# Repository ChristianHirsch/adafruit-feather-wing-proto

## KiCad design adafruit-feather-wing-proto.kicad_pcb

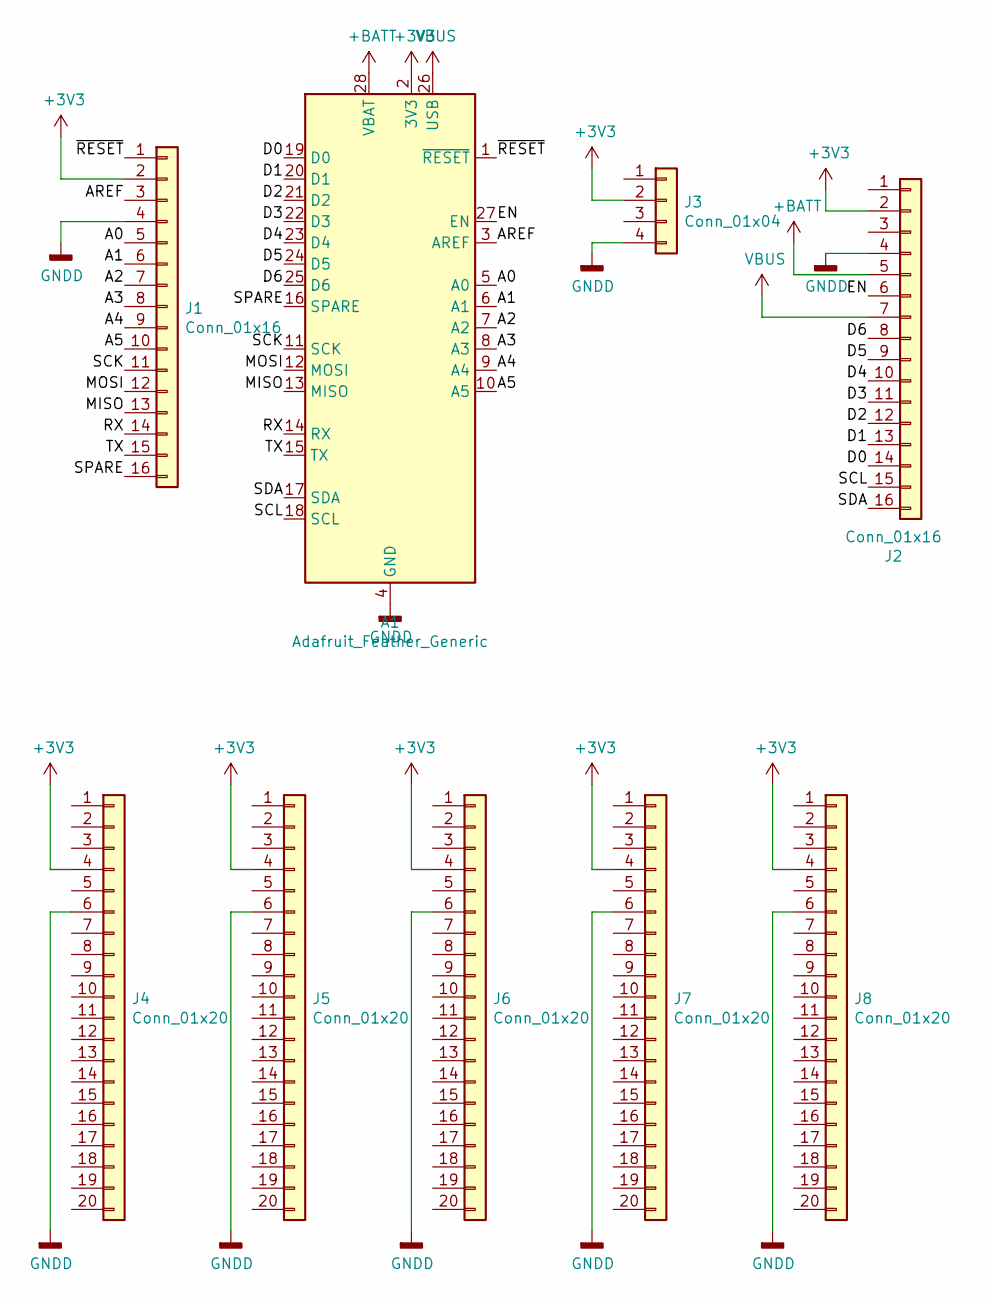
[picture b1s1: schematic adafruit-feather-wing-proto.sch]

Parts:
A1: Adafruit_Feather_Generic; Adafruit_Feather_WithMountingHoles
J1, J2: Conn_01x16; PinSocket_1x16_P2.54mm_Vertical
J3: Conn_01x04; PinSocket_1x04_P2.54mm_Vertical
J4, J5, J6, J7, J8: Conn_01x20; PinSocket_1x20_P2.54mm_Vertical

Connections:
+3V3: A1.2 (3V3), J1.2, J2.2, J3.2, J4.4, J5.4, J6.4, J7.4, J8.4
+BATT: A1.28 (VBAT), J2.5
/A0: A1.5 (A0), J1.5
/A1: A1.6 (A1), J1.6
/A2: A1.7 (A2), J1.7
/A3: A1.8 (A3), J1.8
/A4: A1.9 (A4), J1.9
/A5: A1.10 (A5), J1.10
/AREF: A1.3 (AREF), J1.3
/D0: A1.19 (D0), J2.14
/D1: A1.20 (D1), J2.13
/D2: A1.21 (D2), J2.12
/D3: A1.22 (D3), J2.11
/D4: A1.23 (D4), J2.10
/D5: A1.24 (D5), J2.9
/D6: A1.25 (D6), J2.8
/EN: A1.27 (EN), J2.6
/MISO: A1.13 (MISO), J1.13
/MOSI: A1.12 (MOSI), J1.12
/RX: A1.14 (RX), J1.14
/SCK: A1.11 (SCK), J1.11
/SCL: A1.18 (SCL), J2.15
/SDA: A1.17 (SDA), J2.16
/SPARE: A1.16 (SPARE), J1.16
/TX: A1.15 (TX), J1.15
/~RESET: A1.1 (~RESET), J1.1
GNDD: A1.4 (GND), J1.4, J2.4, J3.4, J4.6, J5.6, J6.6, J7.6, J8.6
VBUS: A1.26 (USB), J2.7

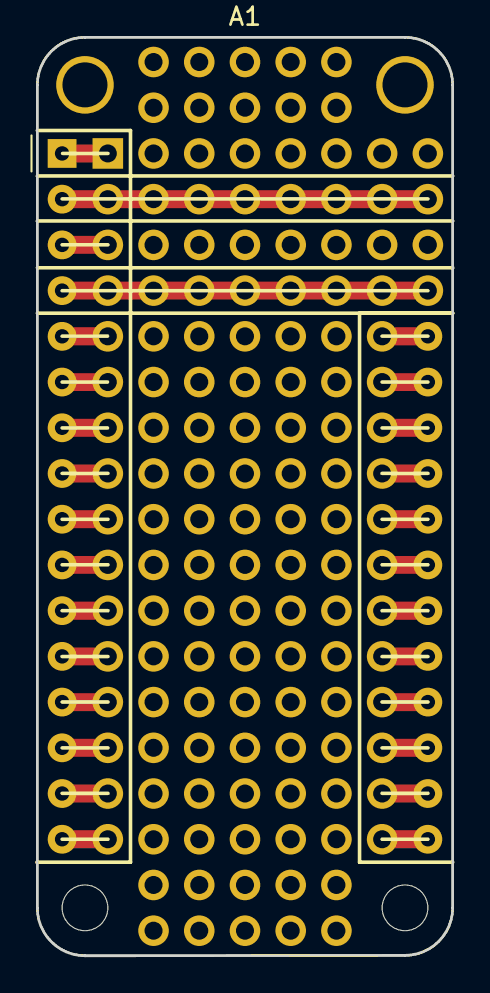
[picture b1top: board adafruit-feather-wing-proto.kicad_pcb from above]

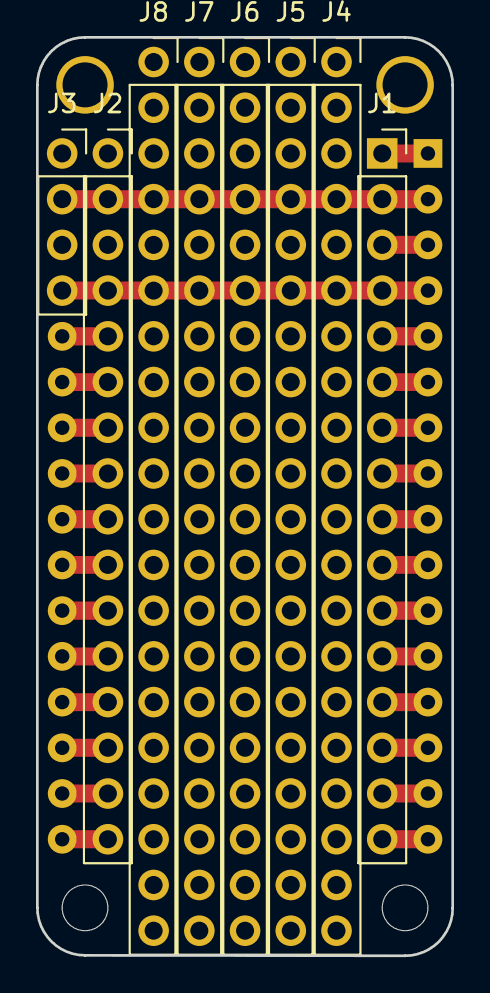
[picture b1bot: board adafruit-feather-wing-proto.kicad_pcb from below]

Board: 2 copper layers, 23.1 x 51.0 mm, 9 parts (8 on the bottom side), 28 nets.
